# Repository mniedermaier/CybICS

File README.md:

<p align="center">
  <b>A complete industrial facility on your desk. Attack it. Detect it. Defend it.</b><br/>
  Open-source ICS security training, on a Raspberry Pi board or in Docker.<br/>
  <sub>CybICS is pronounced "Cybix".</sub>
</p>

<div align="center">

</div>

---

## What is CybICS?

CybICS (Cybersecurity for Industrial Control Systems) is an open-source training platform designed to help cybersecurity professionals, students, and researchers understand the unique challenges of securing industrial control systems (ICS) and SCADA environments.

The platform recreates a complete industrial facility, from the physical process up to the operator's screen:
- **Physical process** - a gas pressure process with tanks, a compressor and valves, run by an STM32 on the board or simulated in Docker
- **PLC** (Programmable Logic Controller) - OpenPLC
- **HMI** (Human-Machine Interface) - FUXA
- **Gateways and services** - an OPC-UA server and an S7comm endpoint
- **Engineering workstation and attack machine** - the tools of the operator and of the attacker
- **Intrusion detection** - a rule-based IDS watching the plant network
- **Industrial protocols** - Modbus TCP, OPC-UA and S7comm, plus DNP3 and EtherNet/IP via OpenPLC

### Why CybICS?

- **A real plant, not only a VM.** The physical board is the process diagram: LEDs show the tanks, the compressor and the valves as you attack them. The same process runs in Docker when no board is at hand.
- **Learn, attack, detect, defend.** 38 Theory Path lessons, 22 CTF challenges and a built-in IDS, mapped to MITRE ATT&CK for ICS, D3FEND and NIST SP 800-82r3.
- **Real industrial protocols.** Modbus TCP, S7comm and OPC-UA against OpenPLC and a FUXA HMI.
- **Free and open source.** The CybICS hardware, firmware and software are MIT licensed.

---

## Table of Contents

- [What is CybICS?](#what-is-cybics)
- [Deployment Options](#deployment-options)
- [Quick Start - Virtual Testbed](#quick-start---virtual-testbed)
- [Physical Process Description](#physical-process-description)
- [Hardware](#hardware)
- [Software Components](#software-components)
- [Training Modules](#training-modules)
- [Troubleshooting](#troubleshooting)
- [Documentation](#documentation)
- [Abbreviations](#abbreviations)
- [Contributing](#contributing)
- [License](#license)

---

## Deployment Options

CybICS offers two deployment modes to suit different learning needs and budgets:

<table>
<tr>
<td width="50%" valign="top">

### Virtual (Recommended for Beginners)
**Docker-based deployment for easy setup**

</td>
<td width="50%" valign="top">

### Physical (Advanced)
**Hardware-based deployment with Raspberry Pi**

</td>
</tr>
<tr>
<td width="50%" valign="top">

**Advantages**:
- No hardware required
- Quick setup (5 minutes)
- Easy to reset and reproduce
- Suited to classroom and online training
- Runs on Windows, Linux, macOS

</td>
<td width="50%" valign="top">

**Advantages**:
- Realistic physical hardware
- Learn embedded systems security
- Practice hardware attacks (UART, SWD)
- Portable standalone device
- Visual LED indicators

</td>
</tr>
<tr>
<td width="50%" valign="top">

**Requirements**:
- Docker & Docker Compose
- 4GB RAM minimum
- 10GB disk space

</td>
<td width="50%" valign="top">

**Requirements**:
- Raspberry Pi Zero 2 W
- Custom CybICS PCB (~50 EUR)
- LCD display
- MicroSD card

</td>
</tr>
<tr>
<td width="50%" valign="top">

**Use Cases**:
- Learning ICS security fundamentals
- Developing attack/defense techniques
- Classroom training sessions
- CTF competitions

</td>
<td width="50%" valign="top">

**Use Cases**:
- Advanced ICS security training
- Hardware hacking workshops
- Demonstrations at conferences
- Permanent lab installations

</td>
</tr>
</table>

---

## Quick Start - Virtual Testbed

Get CybICS running in under 5 minutes using the virtual environment!

### Prerequisites

- **Docker** and **Docker Compose** installed
- **Git** for cloning the repository
- At least 4GB of free RAM
- Linux, macOS, or Windows with WSL2

### Installation

1. **Clone the repository**:
   ```bash
   git clone https://github.com/mniedermaier/CybICS.git --recursive
   cd CybICS
   ```

2. **Start the virtual environment**:
   ```bash
   ./cybics.sh start
   ```

3. **Access the services**:

   Once started, open your browser and navigate to:

   | Service | URL | Default Credentials |
   |---------|-----|---------------------|
   | **Landing Page** | http://localhost | - |

### Managing the Environment

```bash
# Check status of all services
./cybics.sh status

# View logs from all containers
./cybics.sh logs

# Stop the environment
./cybics.sh stop

# Restart the environment
./cybics.sh restart

# Update Docker images to latest version
./cybics.sh update
```
---

## Physical Process Description

CybICS simulates a gas pressure control system commonly found in industrial environments. This simple yet realistic process provides an excellent foundation for learning ICS cybersecurity concepts.

### System Overview

The system maintains gas pressure in a High Pressure Tank (HPT) using gas from a Gas Storage Tank (GST). A PLC controls a compressor that transfers gas between tanks while monitoring pressure levels and safety conditions.

### Components

#### Gas Storage Tank (GST)
Buffer tank for the external gas supply. The PLC maintains GST pressure between 60-240 bar.

| Pressure | Status | Range (bar) | Color Indicator |
|----------|--------|-------------|-----------------|
| <50 | Low | 0-49 | Red |
| 50-149 | Normal | 50-149 | Green |
| 150+ | Full | 150-255 | Blue |

**Control Loop**:
- When GST < 60 bar → Start filling from external supply
- Continue until GST ≥ 240 bar → Stop filling
- Prevents compressor operation when GST is too low

#### High Pressure Tank (HPT)
Main buffer tank providing pressure to the system. Target range: 60-90 bar.

| Pressure | Status | Range (bar) | Meaning |
|----------|--------|-------------|---------|
| 0 | Empty | 0 | System offline |
| 1-49 | Low | 1-49 | Below operating range |
| 50-99 | Normal | 50-99 | Safe operating range |
| 100-149 | High | 100-149 | Above target, but safe |
| 150+ | Critical | 150+ | Dangerous overpressure |

**Control Loop**:
- When HPT < 60 bar AND GST > 50 bar → Start compressor
- Continue until HPT ≥ 90 bar → Stop compressor
- Compressor disabled if GST < 50 bar (safety interlock)

#### System Operation
The system can operate normally when HPT is between 50-100 bar:
- HPT < 50 bar → System cannot operate (insufficient pressure)
- HPT > 100 bar → System at risk of damage

#### Safety: Blowout Valve (BO)
Mechanical safety valve (not PLC-controlled) that prevents catastrophic failure:
- Opens when HPT > 220 bar
- Vents toxic gas to atmosphere
- Closes when HPT < 200 bar
- **Security implication**: Triggering the blowout releases toxic gas

---

## Hardware

For those choosing the physical deployment, CybICS uses affordable, off-the-shelf components.

**Detailed instructions**: [Hardware Guide](hardware/README.md) | [PCB Ordering Guide](hardware/pcb/README.md)

---

## Training Modules

CybICS includes 13+ hands-on training modules covering the full ICS security lifecycle:

Each module includes:
- Background theory
- Hands-on exercises
- CTF-style flags
- Hints and solutions

**Start training**: [Training Overview](training/README.md)

---

## Documentation

Comprehensive documentation is available for all components:

### Getting Started
- [Quick Start Guide](doc/README.md) - Detailed installation instructions
- [Training Overview](training/README.md) - All training modules
- [Testing Guide](tests/README.md) - Automated testing

### Hardware
- [Hardware Overview](hardware/README.md) - BOM, assembly, specifications
- [PCB Ordering Guide](hardware/pcb/README.md) - Step-by-step JLCPCB ordering
- [3D Case Files](hardware/case/README.md) - Printable enclosure

### Software
- [Software Overview](software/README.md) - Setup and configuration
- [OpenPLC Integration](software/OpenPLC/README.md) - PLC programming and configuration
- [FUXA HMI](software/FUXA/README.md) - HMI configuration
- [Virtual Hardware I/O](software/hwio-virtual/README.md) - Virtual process simulation
- [Raspberry Pi I/O](software/hwio-raspberry/README.md) - Physical hardware interface
- [STM32 Firmware](software/stm32/README.md) - Embedded firmware (Zephyr RTOS)

---

## Abbreviations

| Abbreviation | Full Name | Description |
| ------------ | --------- | ----------- |
| **BO** | Blowout | Safety valve that vents gas at critical pressure |
| **CTF** | Capture The Flag | Security training challenge format |
| **DNP3** | Distributed Network Protocol 3 | SCADA communication protocol |
| **GST** | Gas Storage Tank | Buffer tank for external gas supply |
| **HMI** | Human-Machine Interface | Operator control and monitoring interface |
| **HPT** | High Pressure Tank | Main system pressure buffer |
| **I2C** | Inter-Integrated Circuit | Serial communication protocol |
| **ICS** | Industrial Control System | Systems controlling industrial processes |
| **LED** | Light-Emitting Diode | Visual indicator on hardware |
| **OPC-UA** | OPC Unified Architecture | Industry 4.0 communication standard |
| **PCB** | Printed Circuit Board | CybICS custom hardware board |
| **PLC** | Programmable Logic Controller | Industrial controller (OpenPLC) |
| **RTOS** | Real-Time Operating System | Zephyr (on STM32) |
| **SCADA** | Supervisory Control and Data Acquisition | Industrial monitoring system |
| **STM32** | STMicroelectronics 32-bit MCU | Microcontroller on CybICS PCB |
| **SWD** | Serial Wire Debug | Programming/debugging interface for STM32 |
| **UART** | Universal Asynchronous Receiver-Transmitter | Serial communication |

---

## Contributing

We welcome contributions from the community! Here's how you can help:

### Ways to Contribute

- **Report bugs** via GitHub Issues
- **Suggest features** or improvements
- **Improve documentation** (typos, clarity, examples)
- **Create training modules** for new attack/defense techniques
- **Submit code improvements** via Pull Requests
- **Translate documentation** to other languages

### Development Setup

1. Fork the repository
2. Clone your fork: `git clone --recursive https://github.com/YOUR_USERNAME/CybICS.git`
3. Create a branch: `git checkout -b feature/your-feature-name`
4. Make your changes
5. Start the stack and run the full test suite: `./cybics.sh start && pytest tests/`
6. Commit using [Conventional Commits](https://www.conventionalcommits.org/): `git commit -m "feat(landing): describe the change"`
7. Push: `git push origin feature/your-feature-name`
8. Open a Pull Request describing the cause, the fix and what you verified

Everything in git and on GitHub is written in English. The full set of
conventions, including the places that must be changed together, is in
[CLAUDE.md](CLAUDE.md). It is written for AI assistants but applies to everyone.

---

## Build Status

## License

CybICS is released under the **MIT License**. See [LICENSE](/LICENSE) for details.

### Third-Party Components

- **OpenPLC**: GPL-3.0 License
- **FUXA**: MIT License
- **Zephyr RTOS**: Apache-2.0 License

---

## Acknowledgments

CybICS is developed for educational purposes to improve ICS cybersecurity awareness. Special thanks to the open-source community and all contributors.

**Disclaimer**: This platform is designed for authorized training and education only. Unauthorized use against production systems is illegal and unethical.

---

<p align="center">
  <strong>Ready to start?</strong><br>
  <code>./cybics.sh start</code>
</p>

<p align="center">
  <a href="doc/README.md">Detailed Setup Guide</a> •
  <a href="training/README.md">Training Modules</a> •
  <a href="https://github.com/mniedermaier/CybICS/issues">Report Issues</a>
</p>

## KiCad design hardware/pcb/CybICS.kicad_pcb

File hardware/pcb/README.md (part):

# CybICS PCB Ordering Guide

## Overview
This guide provides detailed instructions for ordering the CybICS PCB from JLCPCB with full assembly service. The PCB is designed to be manufactured and assembled by JLCPCB, eliminating the need for manual soldering.

## PCB Design Files
The PCB is designed using KiCad 10.x and all source files are available in this
directory. The sources are stored in the KiCad 10 file format, so KiCad 8 and 9
cannot open them -- install KiCad 10 or later before doing anything below:
- **Schematic**: Shows the circuit design and connections
- **PCB Layout**: Physical board design with component placement
- **Gerber Files**: Manufacturing files for PCB fabrication
- **BOM (Bill of Materials)**: List of all components
- **CPL (Component Placement List)**: Positions for automated assembly

### Project 3D models

`cybics.3dshapes/` holds the models KiCad does not ship. Each one that was
generated rather than downloaded keeps its build script next to it, so it can
be regenerated instead of being an unmaintainable binary:

| Model | Source | Notes |
|-------|--------|-------|
| `Raspberry_Pi_Zero.step` | `Raspberry_Pi_Zero.build.py` (CadQuery) | J1's second model, so the Pi appears plugged onto the board |
| `LCD1602.step` | `LCD1602.build.py` (CadQuery) | DS1; replaces KiCad's `WC1602A.step` |
| `SW-SMD_8P-...step/.wrl` | vendor download (LCSC C2858287) | navigation switch SW3 |
| `USB_C_Receptacle_G-Switch_GT-USB-7010ASV.wrl` | `easyeda2kicad --lcsc_id=C2988369` | J4; KiCad ships no model for this footprint |

The Pi Zero model sits 11.0 mm above the board: 2.5 mm for the male header body
on the carrier plus 8.5 mm for the socket on the Pi's underside, which is the
standard Pi HAT spacing. The Pi is mounted **component side up** -- despite
"FaceDown" in the footprint name -- so the model puts every part on the top
face. Check `doc/pics/cybics.png` if in doubt; that photograph is what the
model was built against.

Outline, mounting holes and the three edge-connector centres come from the
official mechanical drawing; component positions are measured off that
photograph and agree with the drawing's connector centres to about 0.4 mm,
which is what fixes the scale. The parts are simplified shapes rather than
vendor geometry, but carry the detail that makes a render readable:
silkscreen frame and lettering, plated rings around the mounting holes,
the raspberry on the SiP, a stamped microSD lid, recessed connector
mouths, gold test pads, and passives split into black chip resistors and
pale MLCCs the way the photograph shows them.

The female 2x20 socket on the Pi's underside is modelled, with a hole at each
pin position so it mates with the board's male header instead of intersecting
it. It is drawn 0.05 mm short on purpose: the stock header model's body
measures 2.53 mm rather than the nominal 2.50, which would otherwise leave a
sliver of overlap across the whole connector and make every clash check report
it.

Two caveats. The PCB thickness of 1.4 mm is an assumption, as the drawing does
not state one. And the microSD card protrudes 2.1 mm past the board edge, which
is outside J1's `F.Fab` envelope -- that is real, not an error, and worth
knowing when designing an enclosure.

### The display

KiCad's `Display.3dshapes/WC1602A.step` is one fused solid, so the whole module
takes a single colour: pale green board, grey frame, blank white screen. The
replacement splits it into parts and colours them from the photograph -- dark
green board, black bezel, vivid blue screen -- and draws the characters as a
real 5 x 8 dot matrix, because a smooth outline font does not read as an LCD.
The screen shows `CybICS` and nothing more: the firmware also prints a version
and an uptime there, but both would go stale in a file nobody thinks to
regenerate.

Its envelope was recovered by slicing the stock model in Z and matches it
exactly (80 x 36 x 15 mm), so it drops in at the same place.

Regenerate either model with:

```bash
cd hardware/pcb/cybics.3dshapes
python3 -m venv .venv && .venv/bin/pip install cadquery
.venv/bin/python Raspberry_Pi_Zero.build.py
.venv/bin/python LCD1602.build.py
```

`J4` used to render as nothing at all. The board pointed at
`${KICAD10_3DMODEL_DIR}/Connector_USB.3dshapes/USB_C_Receptacle_G-Switch_GT-USB-7010ASV.step`,
which is exactly what the KiCad 10 library footprint declares -- but that file
does not exist. Not locally, and not upstream: `Connector_USB.3dshapes` holds 13
models in total and none of them is a G-Switch part, so 62 of the library's 75
USB footprints have no model. An earlier note here blamed the Ubuntu package;
that was wrong, `kicad-packages3d` 10.0.6 is complete at 3.2 GB and 7251 STEP
files. Installing more would never have fixed it.

The model now comes from the vendor via `easyeda2kicad`, the same route the
navigation switch took, and lives in `cybics.3dshapes/`.

**Vendor models do not share KiCad's footprint origin.** The EasyEDA footprint
for this part sits 1.325 mm in +Y from the KiCad library one, so the model
carries `(offset (xyz 0 1.325 0))` -- note that the offset's Y is negated
relative to the footprint's Y. The way to check an offset is not to reason about
the sign but to compare extents: with this offset the model spans
x -4.470..4.470 and y -3.675..4.225, against the footprint's `F.Fab` at
x -4.470..4.470 and y -3.675..3.675. X matches exactly and so does the front
edge; the 0.55 mm at the back is the shield tab, which `F.Fab` does not draw.

**A model's `.step` and `.wrl` need not share an origin either.** `SW3`'s do
not: the STEP has its origin at the top of the switch body, the VRML at the
board surface. A Z offset measured on one and applied to the other put the
switch 1.85 mm in the air in every render. The board references the `.wrl`, so
measure that one.

## Prerequisites

### Software Requirements
1. **KiCad** (version 10.0 or later)
   - Download from: https://www.kicad.org/download/
   - Used to view and modify PCB design files
   - On Ubuntu, the KiCad project's PPA carries current releases:
     `sudo add-apt-repository ppa:kicad/kicad-10.0-releases && sudo apt install kicad`

2. **Fabrication Toolkit Plugin** (for KiCad)
   - Install via KiCad Plugin and Content Manager
   - Generates files compatible with JLCPCB

### JLCPCB Account
- Create a free account at: https://jlcpcb.com/
- No credit card required for registration

## Step-by-Step Ordering Process

### Step 1: Open the PCB in KiCad

1. Launch KiCad
2. Open the CybICS project file (`.kicad_pro`)
3. Open the PCB Editor
4. Review the design to ensure it's correct

### Step 2: Install Fabrication Toolkit

1. In KiCad, go to **Tools** → **Plugin and Content Manager**
2. Search for "Fabrication Toolkit"
3. Click "Install" and wait for installation to complete
4. Restart KiCad if prompted

<table align="center"><tr><td align="center" width="9999">
</img>
</td></tr></table>

<table align="center"><tr><td align="center" width="9999">
</img>
</td></tr></table>

### Step 3: Generate Fabrication Files

1. Open the PCB Editor in KiCad
2. Click on the **Fabrication Toolkit** icon in the toolbar
3. Tick **Exclude DNP components from BOM**. This one is **off** by default and
   must be changed. `R40` and `R46` are marked DNP because their absence is what
   encodes hardware v1.1, and the plugin keeps DNP parts out of the CPL
   unconditionally but out of the BOM only when this box is ticked. Leave it off
   and the two files disagree: JLCPCB's BOM/CPL matching then reports
   designators that have no position, which is the failure of #238 with the
   files the other way round.
4. Leave the rest of the export options at their defaults. The plugin targets
   JLCPCB already, so there is no manufacturer to choose -- earlier revisions of
   this guide described a **Manufacturer** dropdown that the plugin does not
   have. In particular leave **Plot all active layers** switched off: this is a
   two-layer board, and enabling it only adds the fabrication and courtyard
   layers to the archive, which JLCPCB does not need.
5. Click **Generate** to create all necessary files

<table align="center"><tr><td align="center" width="9999">
</img>
</td></tr></table>

<table align="center"><tr><td align="center" width="9999">
</img>
</td></tr></table>

The toolkit writes `hardware/pcb/production/` (gitignored):
- `CybICS.zip` - gerbers and the PTH/NPTH drill files
- `bom.csv` - bill of materials, JLCPCB column layout
- `positions.csv` - the CPL
- `designators.csv`, `netlist.ipc` - not needed by JLCPCB

### Generating the same files without the GUI

The plugin ships a CLI, so the set can be regenerated reproducibly -- useful for
checking a change without clicking through the dialog. It needs `pcbnew`, so run
it in the image CI already uses:

```bash
curl -sL https://github.com/bennymeg/Fabrication-Toolkit/archive/refs/tags/5.3.1.tar.gz \
  | tar -xz --one-top-level=ft --strip-components=1
docker run --rm --user $(id -u):$(id -g) -e HOME=/tmp \
  -v "$PWD/ft:/ft" -v "$PWD:/repo" -w /ft setsoft/kicad_auto:ki10 \
  python3 -m plugins.cli -p /repo/hardware/pcb/CybICS.kicad_pcb -t -f -e -nI -nB
```

`-t` and `-f` are the automatic translations and zone fill, which the dialog has
on by default and the CLI does not. `-e` is the DNP exclusion from step 3. The
plugin reads the board and writes `production/`; it does not modify the
schematic, the board or the project file.

Whatever route you take, check the two files agree before uploading:

```bash
python3 - <<'EOF'
import csv
bom=list(csv.DictReader(open('hardware/pcb/production/bom.csv',encoding='utf-8-sig')))
cpl=list(csv.DictReader(open('hardware/pcb/production/positions.csv',encoding='utf-8-sig')))
b={r.strip() for row in bom for r in row['Designator'].split(',')}
c={r['Designator'] for r in cpl}
print('BOM only:', sorted(b-c) or 'none')
print('CPL only:', sorted(c-b) or 'none')
for x in ('R40','R46','FID1','FID2','FID3'):
    assert x not in b and x not in c, x
print('no DNP or fiducials in either file')
EOF
```

### Step 4: Upload to JLCPCB

1. Go to https://jlcpcb.com/
2. Click **Quote Now** or **Instant Quote**
3. Click **Add Gerber File** and upload `gerber.zip`
4. Wait for the system to process the file (~30 seconds)

### Step 5: Configure PCB Options

After upload, configure the following options:

### Step 6: Enable PCB Assembly

1. Scroll down and toggle **PCB Assembly** to ON

### Step 7: Upload BOM and CPL Files

1. Click **Confirm** on the assembly section
2. Upload the BOM file:
   - Click **Add BOM File**
   - Select `bom.csv` from the production folder
3. Upload the CPL file:
   - Click **Add CPL File**
   - Select `positions.csv` from the production folder
4. Click **Process BOM & CPL**

### Step 7b: Check the version straps are not placed

`R40` and `R46` are marked **DNP** -- they encode the hardware revision by
being absent (see [Hardware Version Coding](../README.md#version-coding)).
Confirm they are missing from the uploaded BOM and CPL. Do not take the
plugin's word for it: whether they leave the BOM depends on the checkbox in
step 3, and if JLCPCB places them the board reports code `00000` instead of
`00001` and identifies itself as a revision that does not exist.

Every other `R41`-`R44` and `R47`-`R50` must be placed.

### Step 8: Component Matching

After processing, JLCPCB will display component matching:

1. **Review matched components**:
   - Green checkmark: Component found in JLCPCB inventory
   - Yellow warning: Alternative suggested
   - Red X: Component not available

2. **For unavailable components**:
   - Click on the component row
   - Search for alternatives in JLCPCB library

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
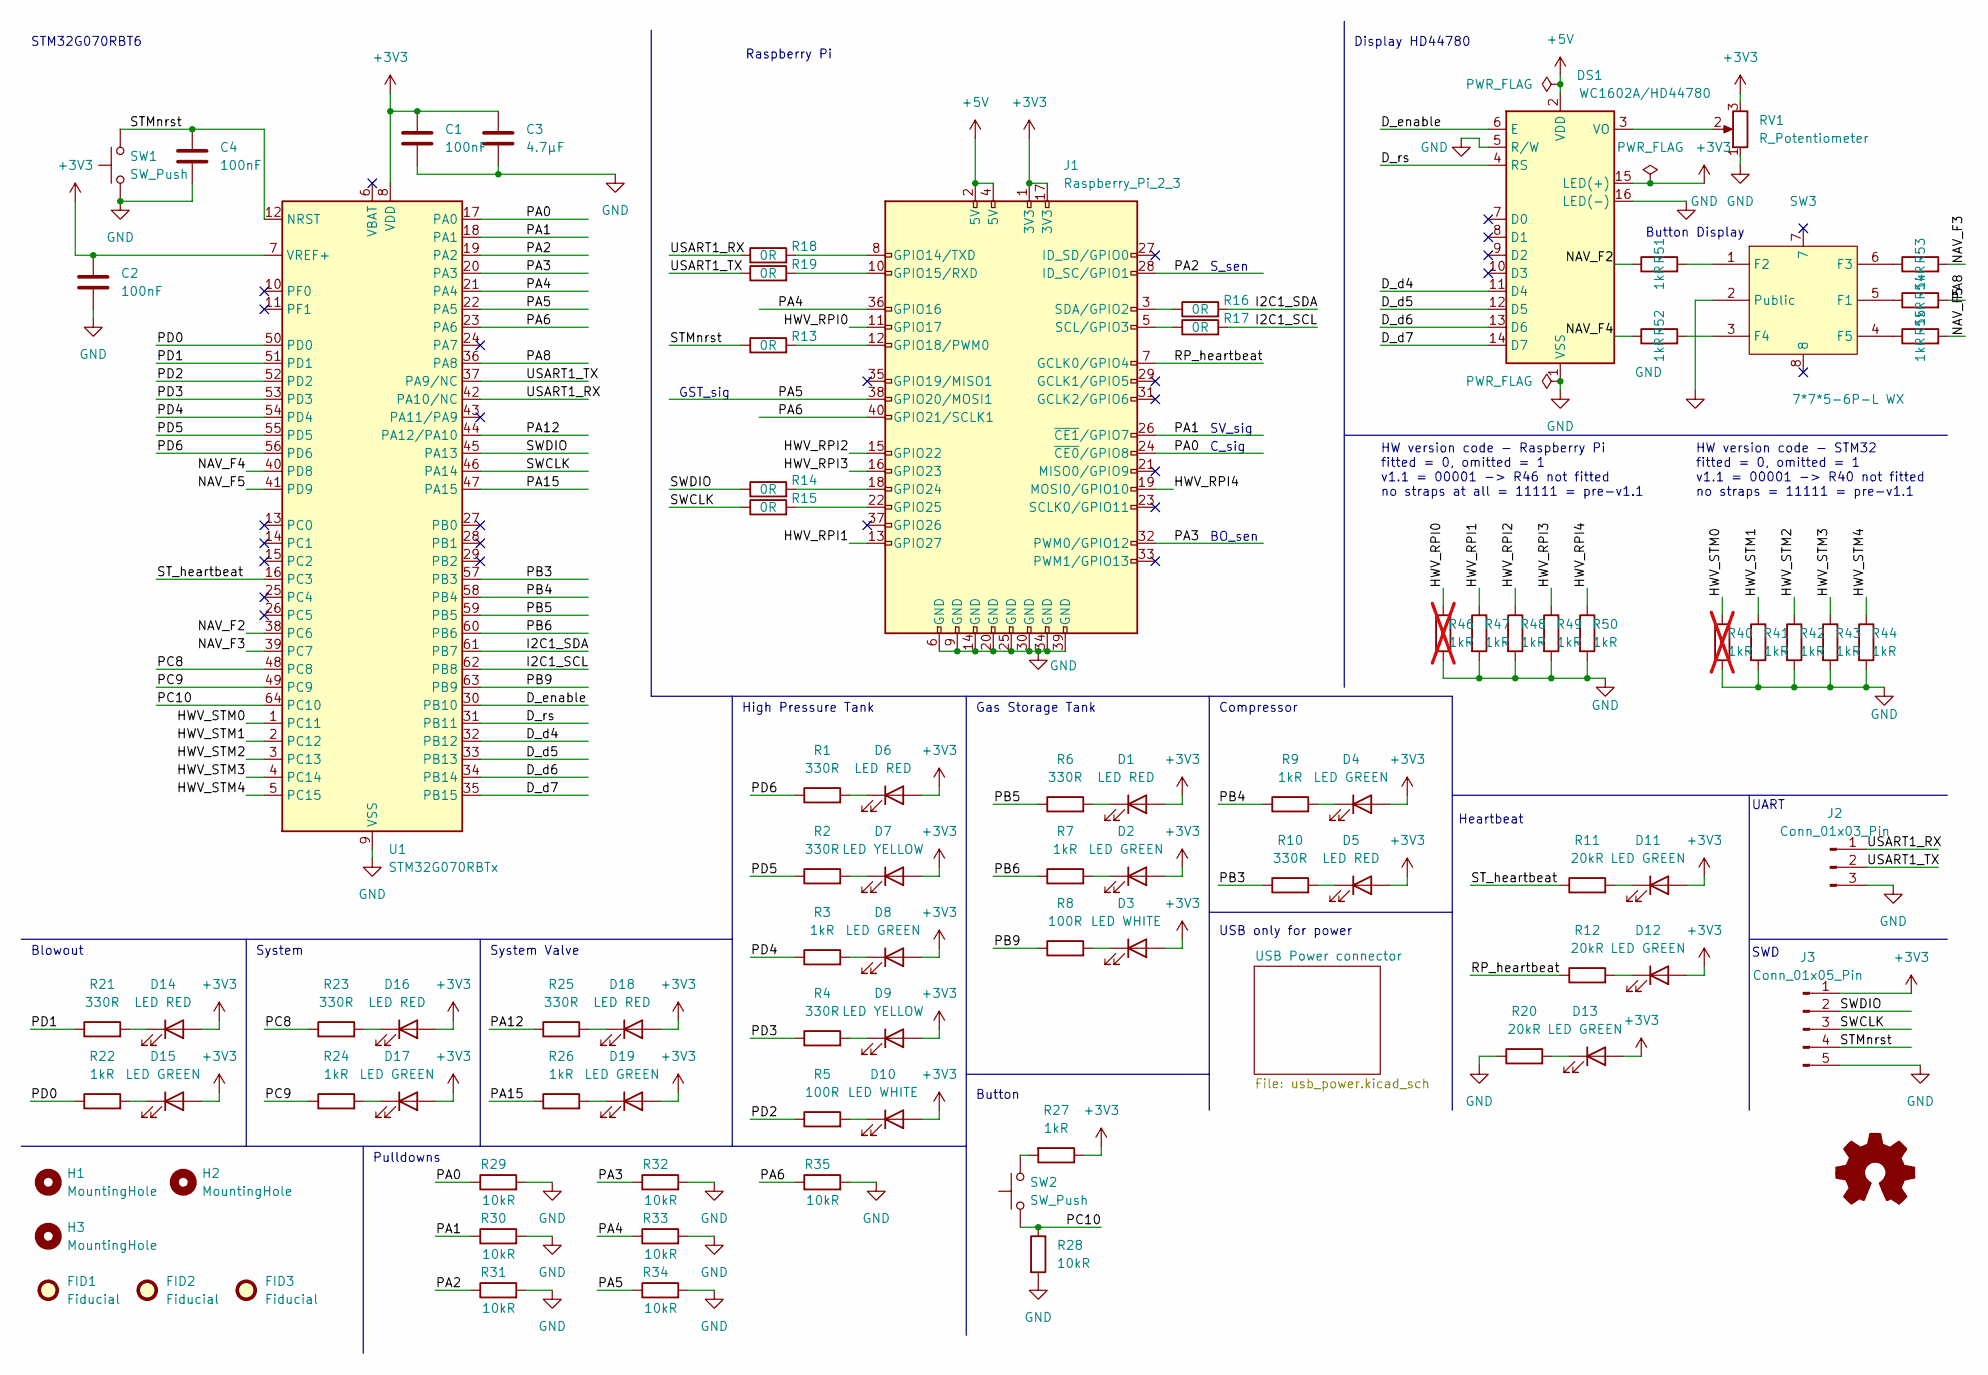
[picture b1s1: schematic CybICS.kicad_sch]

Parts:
C1, C2, C4: 100nF; C_0805_2012Metric_Pad1.18x1.45mm_HandSolder; JLCPCB Part # C49678
C3: 4.7μF; C_0805_2012Metric_Pad1.18x1.45mm_HandSolder; JLCPCB Part # C1779
D1, D5, D6, D14, D16, D18: LED RED; LED_0805_2012Metric_Pad1.15x1.40mm_HandSolder; JLCPCB Part # C84256
D2, D4, D8, D11, D12, D13, D15, D17, D19: LED GREEN; LED_0805_2012Metric_Pad1.15x1.40mm_HandSolder; JLCPCB Part # C2297
D3, D10: LED WHITE; LED_0805_2012Metric_Pad1.15x1.40mm_HandSolder; JLCPCB Part # C34499
D7, D9: LED YELLOW; LED_0805_2012Metric_Pad1.15x1.40mm_HandSolder; JLCPCB Part # C2296
DS1: WC1602A/HD44780; WC1602A; JLCPCB Part # C5307341
FID1, FID2, FID3: Fiducial; Fiducial_1mm_Mask2mm
H1, H2, H3: MountingHole; MountingHole_3.2mm_M3
J1: Raspberry_Pi_2_3; Raspberry_Pi_Zero_Socketed_THT_FaceDown_MountingHoles; JLCPCB Part # C5224014
J2: Conn_01x03_Pin; PinHeader_1x03_P2.54mm_Vertical; JLCPCB Part # C5445396
J3: Conn_01x05_Pin; PinHeader_1x05_P2.54mm_Vertical; JLCPCB Part # C225480
R1, R2, R4, R6, R10, R21, R23, R25: 330R; R_0805_2012Metric_Pad1.20x1.40mm_HandSolder; JLCPCB Part # C17630
R3, R7, R9, R22, R24, R26, R27, R41, R42, R43, R44, R47, R48, R49, R50, R51, R52, R53, R54, R55: 1kR; R_0805_2012Metric_Pad1.20x1.40mm_HandSolder; JLCPCB Part # C17513
R5, R8: 100R; R_0805_2012Metric_Pad1.20x1.40mm_HandSolder; JLCPCB Part # C17408
R11, R12, R20: 20kR; R_0805_2012Metric_Pad1.20x1.40mm_HandSolder; JLCPCB Part # C4328
R13, R14, R15, R16, R17, R18, R19: 0R; R_0805_2012Metric_Pad1.20x1.40mm_HandSolder; JLCPCB Part # C17477
R28, R29, R30, R31, R32, R33, R34, R35: 10kR; R_0805_2012Metric_Pad1.20x1.40mm_HandSolder; JLCPCB Part # C17414
R40, R46: 1kR; R_0805_2012Metric_Pad1.20x1.40mm_HandSolder; JLCPCB Part # C17513; not fitted
RV1: R_Potentiometer; Potentiometer_Bourns_3314J_Vertical; JLCPCB Part # C36376
SW1, SW2: SW_Push; SW_PUSH_6mm_H5mm; JLCPCB Part # C428628
SW3: 7*7*5-6P-L WX; SW-SMD_8P-L7.0-W7.0-P1.40-LS7.4-TL; JLCPCB Part # C2858287
U1: STM32G070RBTx; LQFP-64_10x10mm_P0.5mm; JLCPCB Part # C529340

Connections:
+3V3: C1.1, C2.1, C3.1, D1.2 (A), D2.2 (A), D3.2 (A), D4.2 (A), D5.2 (A), D6.2 (A), D7.2 (A), D8.2 (A), D9.2 (A), D10.2 (A), D11.2 (A), D12.2 (A), D13.2 (A), D14.2 (A), D15.2 (A), D16.2 (A), D17.2 (A), D18.2 (A), D19.2 (A), DS1.15 (LED(+)), J1.1 (3V3), J1.17 (3V3), J3.1, R27.1, RV1.3, U1.7 (VREF+), U1.8 (VDD)
+5V: DS1.2 (VDD), J1.2 (5V), J1.4 (5V); also elsewhere on the board
/D_d4: DS1.11 (D4), U1.32 (PB12)
/D_d5: DS1.12 (D5), U1.33 (PB13)
/D_d6: DS1.13 (D6), U1.34 (PB14)
/D_d7: DS1.14 (D7), U1.35 (PB15)
/D_enable: DS1.6 (E), U1.30 (PB10)
/D_rs: DS1.4 (RS), U1.31 (PB11)
/HWV_RPI0: J1.11 (GPIO17), R46.1
/HWV_RPI1: J1.13 (GPIO27), R47.1
/HWV_RPI2: J1.15 (GPIO22), R48.1
/HWV_RPI3: J1.16 (GPIO23), R49.1
/HWV_RPI4: J1.19 (MOSI0/GPIO10), R50.1
/HWV_STM0: R40.1, U1.1 (PC11)
/HWV_STM1: R41.1, U1.2 (PC12)
/HWV_STM2: R42.1, U1.3 (PC13)
/HWV_STM3: R43.1, U1.4 (PC14)
/HWV_STM4: R44.1, U1.5 (PC15)
/I2C1_SCL: R17.2, U1.62 (PB8)
/I2C1_SDA: R16.2, U1.61 (PB7)
/NAV_F2: R51.1, U1.38 (PC6)
/NAV_F3: R53.2, U1.39 (PC7)
/NAV_F4: R52.1, U1.40 (PD8)
/NAV_F5: R55.2, U1.41 (PD9)
/PA0: J1.24 (~CE0/GPIO8), R29.1, U1.17 (PA0)
/PA1: J1.26 (~CE1/GPIO7), R30.1, U1.18 (PA1)
/PA2: J1.28 (ID_SC/GPIO1), R31.1, U1.19 (PA2)
/PA3: J1.32 (PWM0/GPIO12), R32.1, U1.20 (PA3)
/PA4: J1.36 (GPIO16), R33.1, U1.21 (PA4)
/PA5: J1.38 (GPIO20/MOSI1), R34.1, U1.22 (PA5)
/PA6: J1.40 (GPIO21/SCLK1), R35.1, U1.23 (PA6)
/PA8: R54.2, U1.36 (PA8)
/PA12: R25.1, U1.44 (PA12/PA10)
/PA15: R26.1, U1.47 (PA15)
/PB3: R10.1, U1.57 (PB3)
/PB4: R9.1, U1.58 (PB4)
/PB5: R6.1, U1.59 (PB5)
/PB6: R7.1, U1.60 (PB6)
/PB9: R8.1, U1.63 (PB9)
/PC8: R23.1, U1.48 (PC8)
/PC9: R24.1, U1.49 (PC9)
/PC10: R28.1, SW2.1, U1.64 (PC10)
/PD0: R22.1, U1.50 (PD0)
/PD1: R21.1, U1.51 (PD1)
/PD2: R5.1, U1.52 (PD2)
/PD3: R4.1, U1.53 (PD3)
/PD4: R3.1, U1.54 (PD4)
/PD5: R2.1, U1.55 (PD5)
/PD6: R1.1, U1.56 (PD6)
/RP_heartbeat: J1.7 (GCLK0/GPIO4), R12.1
/STMnrst: C4.1, J3.4, R13.1, SW1.2, U1.12 (NRST)
/ST_heartbeat: R11.1, U1.16 (PC3)
/SWCLK: J3.3, R15.1, U1.46 (PA14)
/SWDIO: J3.2, R14.1, U1.45 (PA13)
/USART1_RX: J2.1, R18.1, U1.42 (PA10/NC)
/USART1_TX: J2.2, R19.1, U1.37 (PA9/NC)
GND: C1.2, C2.2, C3.2, C4.2, DS1.1 (VSS), DS1.5 (R/W), DS1.16 (LED(-)), J1.6 (GND), J1.9 (GND), J1.14 (GND), J1.20 (GND), J1.25 (GND), J1.30 (GND), J1.34 (GND), J1.39 (GND), J2.3, J3.5, R20.1, R28.2, R29.2, R30.2, R31.2, R32.2, R33.2, R34.2, R35.2, R40.2, R41.2, R42.2, R43.2, R44.2, R46.2, R47.2, R48.2, R49.2, R50.2, RV1.1, SW1.1, SW3.2 (Public), U1.9 (VSS); also elsewhere on the board
unnamed: D1.1 (K), R6.2
unnamed: D2.1 (K), R7.2
unnamed: D3.1 (K), R8.2
unnamed: D4.1 (K), R9.2
unnamed: D5.1 (K), R10.2
unnamed: D6.1 (K), R1.2
unnamed: D7.1 (K), R2.2
unnamed: D8.1 (K), R3.2
unnamed: D9.1 (K), R4.2
unnamed: D10.1 (K), R5.2
unnamed: D11.1 (K), R11.2
unnamed: D12.1 (K), R12.2
unnamed: D13.1 (K), R20.2
unnamed: D14.1 (K), R21.2
unnamed: D15.1 (K), R22.2
unnamed: D16.1 (K), R23.2
unnamed: D17.1 (K), R24.2
unnamed: D18.1 (K), R25.2
unnamed: D19.1 (K), R26.2
unnamed: DS1.3 (VO), RV1.2
unnamed: J1.8 (GPIO14/TXD), R18.2
unnamed: J1.10 (GPIO15/RXD), R19.2
unnamed: J1.12 (GPIO18/PWM0), R13.2
unnamed: J1.18 (GPIO24), R14.2
unnamed: J1.22 (GPIO25), R15.2
unnamed: J1.5 (SCL/GPIO3), R17.1
unnamed: J1.3 (SDA/GPIO2), R16.1
unnamed: R27.2, SW2.2
unnamed: R54.1, SW3.5 (F1)
unnamed: R51.2, SW3.1 (F2)
unnamed: R53.1, SW3.6 (F3)
unnamed: R52.2, SW3.3 (F4)
unnamed: R55.1, SW3.4 (F5)

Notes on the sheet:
UART
Gas Storage Tank
HW version code - STM32 fitted = 0, omitted = 1 v1.1 = 00001 -> R40 not fitted no straps = 11111 = pre-v1.1
System
High Pressure Tank
STM32G070RBT6
Heartbeat
System Valve
GST_sig
Button
SWD
Display HD44780
Pulldowns
Raspberry Pi
C_sig
HW version code - Raspberry Pi fitted = 0, omitted = 1 v1.1 = 00001 -> R46 not fitted no straps at all = 11111 = pre-v1.1
SV_sig
S_sen
BO_sen
Button Display
USB only for power
Blowout
Compressor

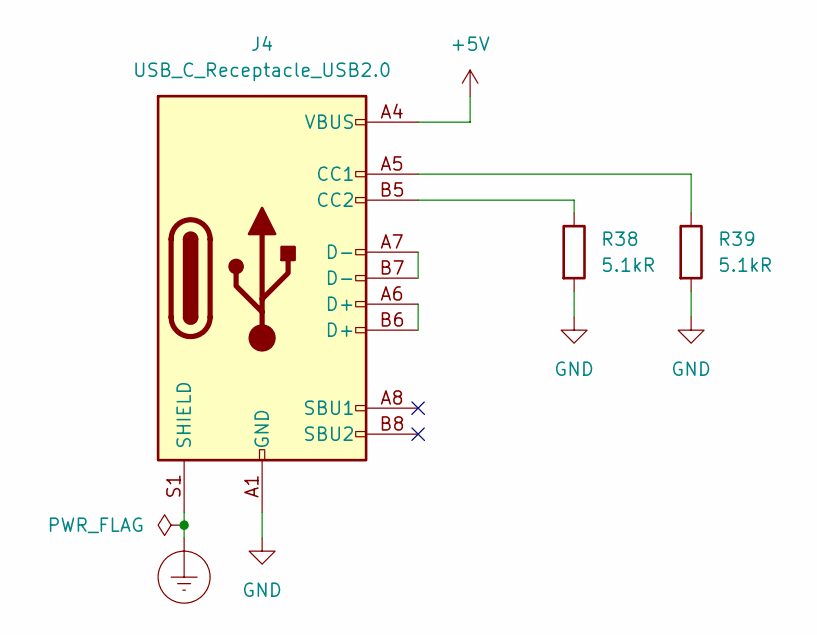
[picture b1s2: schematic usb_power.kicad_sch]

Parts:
J4: USB_C_Receptacle_USB2.0; USB_C_Receptacle_G-Switch_GT-USB-7010ASV; JLCPCB Part # C2988369
R38, R39: 5.1kR; R_0805_2012Metric_Pad1.20x1.40mm_HandSolder; JLCPCB Part # C27834

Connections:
+5V: J4.A4 (VBUS), J4.A9 (VBUS), J4.B4 (VBUS), J4.B9 (VBUS); also elsewhere on the board
Earth_Protective: J4.S1 (SHIELD)
GND: J4.A1 (GND), J4.A12 (GND), J4.B1 (GND), J4.B12 (GND), R38.2, R39.2; also elsewhere on the board
unnamed: J4.A5 (CC1), R39.1
unnamed: J4.B5 (CC2), R38.1
unnamed: J4.A6 (D+), J4.B6 (D+)
unnamed: J4.A7 (D-), J4.B7 (D-)

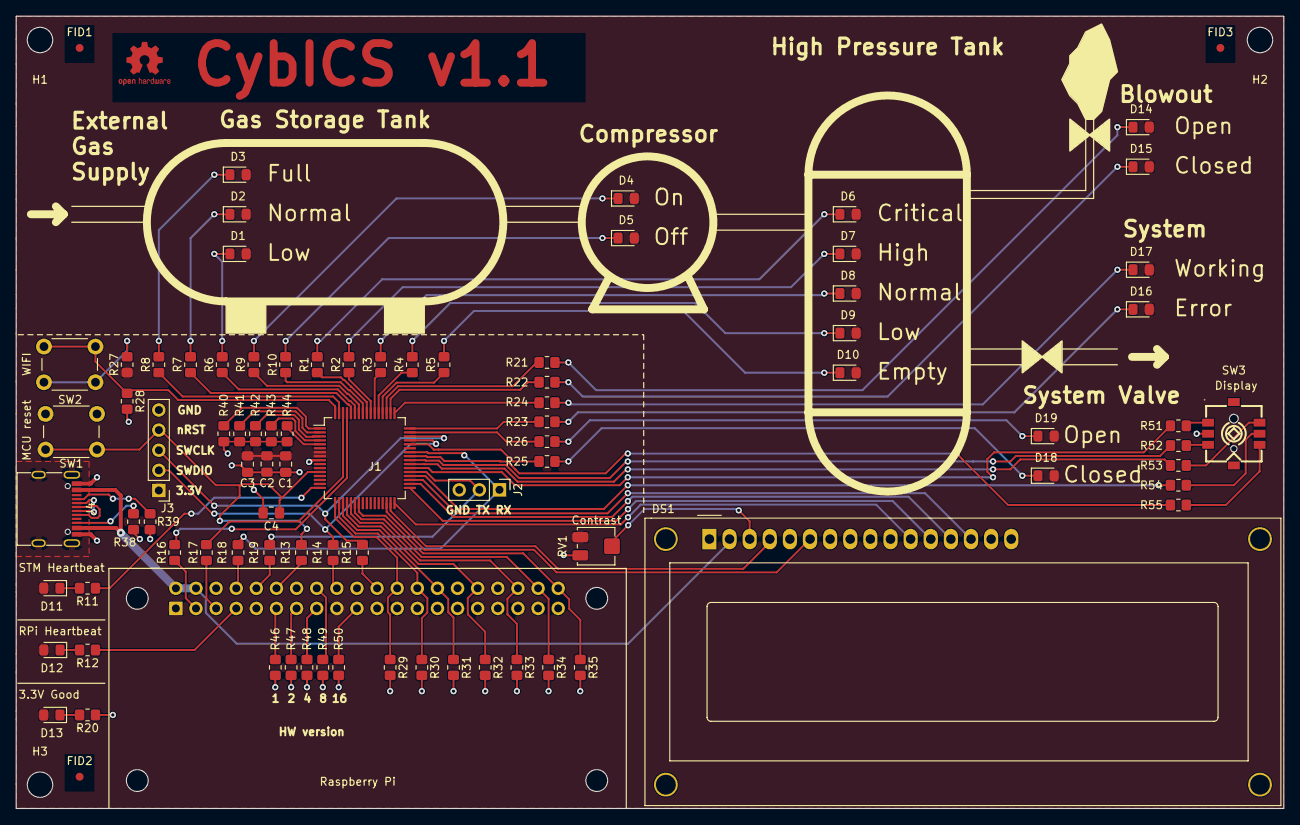
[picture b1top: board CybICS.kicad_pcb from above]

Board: 2 copper layers, 160.0 x 100.0 mm, 91 parts (0 on the bottom side), 94 nets.

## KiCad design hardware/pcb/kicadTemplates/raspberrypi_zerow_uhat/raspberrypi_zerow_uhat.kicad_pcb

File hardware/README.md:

## Hardware  
The hardware was kept simple and cost-efficient.
All you need is the CybICS baseboard, a Raspberry Pi Zero 2 W and a 1602 display.
For the physical process visualization on the PCB a few LEDs are used.

<table align="center"><tr><td align="center" width="9999">
</img>
</td></tr></table>

The PCB can be ordered completly assembled at [JLCPCB](https://jlcpcb.com/).
The total cost for a testbed is around 50 euros.
However, the minimum purchase of PCBs is 5 pieces when ordered from [JLCPCB](https://jlcpcb.com/).

### Components
The hardware consists of three core components.
Additionally, there is a 3D printable case,
which makes desk usage easier ([link](case/README.md)).

| Component        | Description                             |
| ---------------- | --------------------------------------- |
| Base Board       | Simulating the physical process         |
| Raspberry Pi     | Controlling the physical process        |
| Display          | HD44780 1602 LCD showing physical state |

## Bill of Materials (BOM)

### Required Components

| Item | Quantity | Description | Approx. Cost (EUR) | Notes |
|------|----------|-------------|-------------------|-------|
| **CybICS PCB** | 1 | Custom PCB with STM32G070RBT6 | ~40 | Min. order 5 pieces from JLCPCB |
| **Raspberry Pi Zero 2 W** | 1 | 1GHz quad-core ARM Cortex-A53 | ~15 | Includes WiFi and Bluetooth |
| **1602 LCD Display** | 1 | HD44780 compatible, I2C interface | ~3 | Blue or green backlight |
| **MicroSD Card** | 1 | 8GB or larger, Class 10 | ~5 | For Raspberry Pi OS |
| **USB-C Cable** | 1 | Power supply cable | ~3 | 5V/2A minimum |
| **Pin Headers** | 1 set | 2.54mm pitch headers for Raspberry Pi | ~2 | Usually included with RPi |

**Total Estimated Cost**: ~50-70 EUR per complete unit

### Optional Components

| Item | Quantity | Description | Approx. Cost (EUR) | Notes |
|------|----------|-------------|-------------------|-------|
| **3D Printed Case** | 1 | Protective enclosure | ~5 | Filament + printing time |
| **Stand/Base** | 1 | Simple display stand | ~2 | See standSimple/ directory |
| **USB Power Adapter** | 1 | 5V/2.5A wall adapter | ~5 | If not using PC USB |

### Where to Buy

#### PCB Manufacturing
- **JLCPCB**: https://jlcpcb.com/ (Recommended - full assembly available)
  - Upload Gerber files from `hardware/pcb/` directory
  - Select assembly service (PCBA)
  - Minimum order: 5 boards
  - Lead time: ~2 weeks

#### Raspberry Pi
- **Official Raspberry Pi Resellers**: https://www.raspberrypi.com/products/
- Local electronics distributors (varies by country)

#### LCD Display
- Common suppliers: AliExpress, Amazon, local electronics shops
- Search for: "1602 LCD I2C" or "1602A LCD module"

#### MicroSD Card
- Any reputable brand (SanDisk, Samsung, Kingston)
- Minimum 8GB, Class 10 or better recommended

## Hardware Version Coding  

From v1.1 the board carries its revision as a 5-bit code that both controllers
can read back, so firmware can adapt without being told which board it runs on.

Each bit is one 1 k resistor to GND, read against the controller's internal
pull-up: **fitted = 0, omitted = 1**. A new revision therefore only changes
which resistors are placed -- no schematic or layout edit.

| Bit | STM32 | pin | Raspberry Pi | pin |
|-----|-------|-----|--------------|-----|
| 0   | R40   | PC11 | R46 | GPIO17 |
| 1   | R41   | PC12 | R47 | GPIO27 |
| 2   | R42   | PC13 | R48 | GPIO22 |
| 3   | R43   | PC14 | R49 | GPIO23 |
| 4   | R44   | PC15 | R50 | GPIO10 |

Both sides carry the same code, so one resistor per side is omitted for a
given revision.

| Code | Revision |
|------|----------|
| `00001` (1) | v1.1 -- R40 and R46 omitted |
| `11111` (31) | **no straps fitted** -- a pre-v1.1 board, or a new board with the straps missing |

`11111` is what a v1.0 board reads by itself: the resistor footprints do not
exist there, so the pins float and the pull-ups win. Do not assign 31 to a real
revision. Note that a v1.1 board assembled without any straps is
indistinguishable from a v1.0 board.

Firmware must enable the internal pull-up on these pins before reading them.

Both sides read them: `software/stm32/src/hw_version.c` for the STM32's copy and
`software/hwio-raspberry/hw_version.py` for the Pi's. The Pi publishes what it
finds to the landing page, under *Settings -> Board Revision*.

The firmware does not simply read them, though: it probes each pin against both
internal pulls, so it can tell a fitted resistor (holds the pin low either way)
from an empty footprint (follows the pull). That is what lets it count how many
of the five are actually soldered, and a board with **none** fitted is then
resolved through `PA8`, which v1.0 loads with `R36` and v1.1 does not. See
[Front Panel and Board Revision Detection](../software/stm32/README.md#board-revision-detection).

So a v1.1 board assembled without straps is no longer silently mistaken for a
v1.0 board -- it is detected, and the firmware says so in the boot log. Fit
`R41`-`R44` anyway: the probe is a safety net, not a substitute, and it cannot
work while somebody is holding the navigation switch during boot.

## Upgrading and Modifications

### Using Different Raspberry Pi Models
The hardware is designed for Raspberry Pi Zero 2 W but can work with:
- **Raspberry Pi Zero W**: Lower performance but compatible
- **Raspberry Pi 3/4**: Will not perfectly fit

### Custom PCB Modifications
The KiCad project files in `hardware/pcb/` can be modified to:
- Add additional sensors or actuators
- Change LED colors or positions
- Modify STM32 pinout
- Add expansion connectors

## Safety Considerations

⚠️ **Important Safety Notes**:
- Use only 5V power supplies - higher voltages will damage components
- Do not connect/disconnect components while powered
- Ensure proper ESD (electrostatic discharge) precautions when handling PCB
- Keep away from water and conductive materials
- Do not modify PCB traces without proper knowledge

## Support and Resources

- **PCB Design Files**: See `hardware/pcb/` directory
- **3D Case Files**: See `hardware/case/` directory
- **Schematic PDF**: Available in `hardware/pcb/` directory
- **STM32 Firmware**: See `software/stm32/` directory
- **Assembly Guide**: This document

For technical support, please open an issue on the GitHub repository.

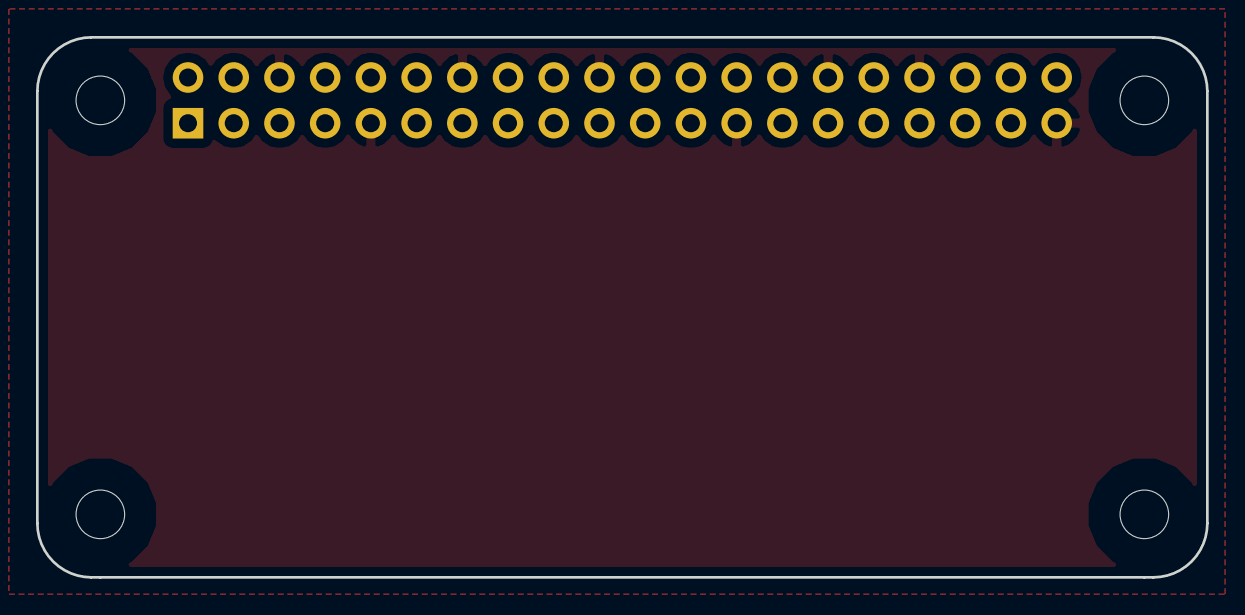
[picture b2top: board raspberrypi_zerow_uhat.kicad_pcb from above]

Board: 2 copper layers, 65.0 x 30.0 mm, 5 parts (1 on the bottom side), 3 nets, no tracks yet.

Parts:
H1, H2, H3, H4: MountingHole; MountingHole_2.7mm_M2.5_uHAT_RPi
J1: GPIO_CONNECTOR; PinSocket_2x20_P2.54mm_Vertical_Centered_Anchor

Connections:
+3V3: J1.1, J1.17
+5V: J1.2, J1.4
GND: J1.6, J1.9, J1.14, J1.20, J1.25, J1.30, J1.34, J1.39

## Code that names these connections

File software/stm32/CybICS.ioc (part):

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Mcu.Name=STM32G070RBTx
Mcu.Package=LQFP64
Mcu.UserName=STM32G070RBTx
PA0.GPIOParameters=GPIO_Label
PA0.GPIO_Label=C_sig
PA0.Signal=GPIO_Input
PA1.GPIOParameters=GPIO_Label
PA1.GPIO_Label=SV_sig
PA1.Signal=GPIO_Input
PA10.GPIOParameters=GPIO_FMPA10,GPIO_Speed,GPIO_PuPd
PA10.GPIO_FMPA10=SYSCFG_FASTMODEPLUS_PA10
PA10.GPIO_PuPd=GPIO_PULLUP
PA10.GPIO_Speed=GPIO_SPEED_FREQ_VERY_HIGH
PA10.Mode=Asynchronous
PA10.Signal=USART1_RX
PA12\ [PA10].GPIOParameters=GPIO_Label
PA12\ [PA10].GPIO_Label=SV_red
PA12\ [PA10].Signal=GPIO_Output
PA13.Mode=Serial_Wire
PA13.Signal=SYS_SWDIO
PA14-BOOT0.Mode=Serial_Wire
PA14-BOOT0.Signal=SYS_SWCLK
PA15.GPIOParameters=GPIO_Label
PA15.GPIO_Label=SV_green
PA15.Signal=GPIO_Output
PA2.GPIOParameters=GPIO_Label
PA2.GPIO_Label=S_sen
PA2.Signal=GPIO_Output
PA3.GPIOParameters=GPIO_Label
PA3.GPIO_Label=BO_sen
PA3.Signal=GPIO_Output
PA4.Signal=GPIO_Input
PA5.GPIOParameters=GPIO_Label
PA5.GPIO_Label=GST_sig
PA5.Signal=GPIO_Input
PA6.Signal=GPIO_Input
PA8.GPIOParameters=GPIO_Label
PA8.GPIO_Label=Display_in
PA8.Signal=GPIO_Input
PA9.GPIOParameters=GPIO_Speed,GPIO_PuPd,GPIO_FMPA9
PA9.GPIO_FMPA9=SYSCFG_FASTMODEPLUS_PA9
PA9.GPIO_PuPd=GPIO_PULLUP
PA9.GPIO_Speed=GPIO_SPEED_FREQ_VERY_HIGH
PA9.Mode=Asynchronous
PA9.Signal=USART1_TX
PB10.GPIOParameters=GPIO_Label
PB10.GPIO_Label=D_enable
PB10.Signal=GPIO_Output
PB11.GPIOParameters=GPIO_Label
PB11.GPIO_Label=D_rs
PB11.Signal=GPIO_Output
PB12.GPIOParameters=GPIO_Label
PB12.GPIO_Label=D_d4
PB12.Signal=GPIO_Output
PB13.GPIOParameters=GPIO_Label
PB13.GPIO_Label=D_d5
PB13.Signal=GPIO_Output
PB14.GPIOParameters=GPIO_Label
PB14.GPIO_Label=D_d6
PB14.Signal=GPIO_Output
PB15.GPIOParameters=GPIO_Label
PB15.GPIO_Label=D_d7
PB15.Signal=GPIO_Output
PB3.GPIOParameters=GPIO_Label
PB3.GPIO_Label=C_off
PB3.Signal=GPIO_Output
PB4.GPIOParameters=GPIO_Label
PB4.GPIO_Label=C_on
PB4.Signal=GPIO_Output
PB5.GPIOParameters=GPIO_Label
PB5.GPIO_Label=GST_low
PB5.Signal=GPIO_Output
PB6.GPIOParameters=GPIO_Label
PB6.GPIO_Label=GST_normal
PB6.Signal=GPIO_Output
PB7.GPIOParameters=GPIO_Speed,GPIO_Pu,GPIO_Mode
PB7.GPIO_Mode=GPIO_MODE_AF_OD
PB7.GPIO_Pu=GPIO_NOPULL
PB7.GPIO_Speed=GPIO_SPEED_FREQ_LOW
PB7.Mode=I2C
PB7.Signal=I2C1_SDA
PB8.GPIOParameters=GPIO_Speed,GPIO_Pu,GPIO_Mode
PB8.GPIO_Mode=GPIO_MODE_AF_OD
PB8.GPIO_Pu=GPIO_NOPULL
PB8.GPIO_Speed=GPIO_SPEED_FREQ_LOW
PB8.Mode=I2C
PB8.Signal=I2C1_SCL
PB9.GPIOParameters=GPIO_Label
PB9.GPIO_Label=GST_full
PB9.Signal=GPIO_Output
PC10.GPIOParameters=GPIO_Label
PC10.GPIO_Label=button
PC10.Signal=GPIO_Input
PC3.GPIOParameters=GPIO_Label
PC3.GPIO_Label=ST_heartbeat
PC3.Signal=GPIO_Output
PC8.GPIOParameters=GPIO_Label
PC8.GPIO_Label=S_red
PC8.Signal=GPIO_Output
PC9.GPIOParameters=GPIO_Label
PC9.GPIO_Label=S_green
PC9.Signal=GPIO_Output
PD0.GPIOParameters=GPIO_Label
PD0.GPIO_Label=BO_green
PD0.Signal=GPIO_Output
PD1.GPIOParameters=GPIO_Label
PD1.GPIO_Label=BO_red
PD1.Signal=GPIO_Output
PD2.GPIOParameters=GPIO_Label
PD2.GPIO_Label=HPT_empty
PD2.Signal=GPIO_Output
PD3.GPIOParameters=GPIO_Label
PD3.GPIO_Label=HPT_low
PD3.Signal=GPIO_Output
PD4.GPIOParameters=GPIO_Label
PD4.GPIO_Label=HPT_normal
PD4.Signal=GPIO_Output
PD5.GPIOParameters=GPIO_Label
PD5.GPIO_Label=HPT_high
PD5.Signal=GPIO_Output
PD6.GPIOParameters=GPIO_Label
PD6.GPIO_Label=HPT_critical
PD6.Signal=GPIO_Output
RCC.HSE_VALUE=8000000
RCC.SYSCLKFreq_VALUE=64000000
RCC.SYSCLKSource=RCC_SYSCLKSOURCE_PLLCLK
board=custom

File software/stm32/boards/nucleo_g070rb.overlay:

/*
 * Copyright (c) 2024 CybICS
 * SPDX-License-Identifier: Apache-2.0
 */

/ {
	aliases {
		led-heartbeat = &heartbeat_led;
	};

	cybics_gpios {
		compatible = "cybics-gpio-group";

		/* Heartbeat LED */
		heartbeat_led: heartbeat_led {
			gpios = <&gpioc 3 GPIO_ACTIVE_HIGH>;
			label = "Heartbeat LED";
		};

		/* Compressor signals */
		c_sig: c_sig {
			gpios = <&gpioa 0 GPIO_ACTIVE_HIGH>;
			label = "Compressor Signal Input";
		};

		c_on: c_on {
			gpios = <&gpiob 4 GPIO_ACTIVE_HIGH>;
			label = "Compressor On LED";
		};

		c_off: c_off {
			gpios = <&gpiob 3 GPIO_ACTIVE_HIGH>;
			label = "Compressor Off LED";
		};

		/* System Valve */
		sv_sig: sv_sig {
			gpios = <&gpioa 1 GPIO_ACTIVE_HIGH>;
			label = "System Valve Signal Input";
		};

		sv_red: sv_red {
			gpios = <&gpioa 12 GPIO_ACTIVE_HIGH>;
			label = "System Valve Red LED";
		};

		sv_green: sv_green {
			gpios = <&gpioa 15 GPIO_ACTIVE_HIGH>;
			label = "System Valve Green LED";
		};

		/* System */
		s_sen: s_sen {
			gpios = <&gpioa 2 GPIO_ACTIVE_HIGH>;
			label = "System Sensor Output";
		};

		s_red: s_red {
			gpios = <&gpioc 8 GPIO_ACTIVE_HIGH>;
			label = "System Red LED";
		};

		s_green: s_green {
			gpios = <&gpioc 9 GPIO_ACTIVE_HIGH>;
			label = "System Green LED";
		};

		/* Blow Out */
		bo_sen: bo_sen {
			gpios = <&gpioa 3 GPIO_ACTIVE_HIGH>;
			label = "Blow Out Sensor Output";
		};

		bo_red: bo_red {
			gpios = <&gpiod 1 GPIO_ACTIVE_HIGH>;
			label = "Blow Out Red LED";
		};

		bo_green: bo_green {
			gpios = <&gpiod 0 GPIO_ACTIVE_HIGH>;
			label = "Blow Out Green LED";
		};

		/* Gas Storage Tank */
		gst_sig: gst_sig {
			gpios = <&gpioa 5 GPIO_ACTIVE_HIGH>;
			label = "GST Signal Input";
		};

		gst_low: gst_low {
			gpios = <&gpiob 5 GPIO_ACTIVE_HIGH>;
			label = "GST Low LED";
		};

		gst_normal: gst_normal {
			gpios = <&gpiob 6 GPIO_ACTIVE_HIGH>;
			label = "GST Normal LED";
		};

		gst_full: gst_full {
			gpios = <&gpiob 9 GPIO_ACTIVE_HIGH>;
			label = "GST Full LED";
		};

		/* High Pressure Tank */
		hpt_empty: hpt_empty {
			gpios = <&gpiod 2 GPIO_ACTIVE_HIGH>;
			label = "HPT Empty LED";
		};

		hpt_low: hpt_low {
			gpios = <&gpiod 3 GPIO_ACTIVE_HIGH>;
			label = "HPT Low LED";
		};

		hpt_normal: hpt_normal {
			gpios = <&gpiod 4 GPIO_ACTIVE_HIGH>;
			label = "HPT Normal LED";
		};

		hpt_high: hpt_high {
			gpios = <&gpiod 5 GPIO_ACTIVE_HIGH>;
			label = "HPT High LED";
		};

		hpt_critical: hpt_critical {
			gpios = <&gpiod 6 GPIO_ACTIVE_HIGH>;
			label = "HPT Critical LED";
		};

		/* Display */
		d_enable: d_enable {
			gpios = <&gpiob 10 GPIO_ACTIVE_HIGH>;
			label = "Display Enable";
		};

		d_rs: d_rs {
			gpios = <&gpiob 11 GPIO_ACTIVE_HIGH>;
			label = "Display RS";
		};

		d_d4: d_d4 {
			gpios = <&gpiob 12 GPIO_ACTIVE_HIGH>;
			label = "Display D4";
		};

		d_d5: d_d5 {
			gpios = <&gpiob 13 GPIO_ACTIVE_HIGH>;
			label = "Display D5";
		};

		d_d6: d_d6 {
			gpios = <&gpiob 14 GPIO_ACTIVE_HIGH>;
			label = "Display D6";
		};

		d_d7: d_d7 {
			gpios = <&gpiob 15 GPIO_ACTIVE_HIGH>;
			label = "Display D7";
		};

	};

	/*
	 * The board's actual buttons.
	 *
	 * Kept apart from cybics_gpios so that "gpio-keys" covers only things
	 * that really are keys.  Nothing binds this today -- the application
	 * polls the pins itself in ui_input.c, because the pull-up and the
	 * polarity differ between board revisions and the devicetree cannot
	 * express a runtime choice.  See ui_input.c for why.
	 *
	 * display_in is the front-panel switch on both revisions:
	 *   v1.0  a discrete push-button, 3V3 -> R37 -> SW3 -> PA8 with R36
	 *         to GND.  Pressed reads high, and an internal pull-up would
	 *         fight R36.
	 *   v1.1+ contact F1, the centre press of the 5-way navigation switch,
	 *         whose common is tied to GND.  Pressed reads low and the pin
	 *         needs the internal pull-up.
	 *
	 * nav_up..nav_right exist only from v1.1.  On a v1.0 board PC6, PC7,
	 * PD8 and PD9 are unconnected, so ui_input.c leaves them unconfigured
	 * there rather than reading four floating pins.
	 */
	cybics_keys {
		compatible = "gpio-keys";

		display_in: display_in {
			gpios = <&gpioa 8 GPIO_ACTIVE_HIGH>;
			label = "Display switch (v1.0 button / v1.1 centre)";
		};

		button: button {
			gpios = <&gpioc 10 GPIO_ACTIVE_HIGH>;
			label = "WiFi Mode Button";
		};

		/*
		 * Navigation switch directions, v1.1 and newer.
		 *
		 * Contact-to-direction comes from the SHOU HAN 7x7x5-6P-L WX
		 * outline drawing (LCSC C2858287, sheet KFC-A07-02-02-2CL): the
		 * moving contact is a diamond and F2, F3, F5, F4 sit clockwise
		 * from its upper-left face, with pins 1..3 on the west edge and
		 * 4..6 on the east.  SW3 is placed unrotated with its locating
		 * posts north and south, so that order maps to up, right, down,
		 * left as seen by someone facing the board.
		 *
		 * ACTIVE_LOW because the switch common is GND.  The pull-up is
		 * applied at runtime, not here, so that one image still serves
		 * v1.0 -- see ui_input.c.
		 */
		nav_up: nav_up {
			gpios = <&gpioc 6 GPIO_ACTIVE_LOW>;
			label = "Navigation up (SW3 F2)";
		};

		nav_right: nav_right {
			gpios = <&gpioc 7 GPIO_ACTIVE_LOW>;
			label = "Navigation right (SW3 F3)";
		};

		nav_down: nav_down {
			gpios = <&gpiod 9 GPIO_ACTIVE_LOW>;
			label = "Navigation down (SW3 F5)";
		};

		nav_left: nav_left {
			gpios = <&gpiod 8 GPIO_ACTIVE_LOW>;
			label = "Navigation left (SW3 F4)";
		};
	};

	/*
	 * Hardware version straps, PC11..PC15 = bit 0..4.
	 *
	 * Each bit is one 1k resistor to GND.  ACTIVE_HIGH makes
	 * gpio_pin_get_dt() return the bit value directly: a fitted strap
	 * holds the pin low (bit 0), an absent one lets the internal pull-up
	 * win (bit 1).
	 *
	 * No GPIO_PULL_UP here, deliberately.  hw_version.c probes each strap
	 * with the pull-down and then the pull-up to tell a fitted resistor
	 * from an unconnected pin, and a pull specified in the devicetree
	 * would be ORed into both configurations and break the pull-down half
	 * of that probe.
	 *
	 * A pre-v1.1 board has no strap footprints at all, so all five pins
	 * float high and read 0b11111.  See the table in
	 * hardware/README.md#version-coding.
	 *
	 * PC14/PC15 double as the LSE oscillator pins; that is safe here
	 * because the board has no crystal and clk_lse stays disabled.
	 */
	cybics_straps {
		compatible = "cybics-gpio-group";

		hw_ver0: hw_ver0 {
			gpios = <&gpioc 11 GPIO_ACTIVE_HIGH>;
			label = "HW version strap bit 0";
		};

		hw_ver1: hw_ver1 {
			gpios = <&gpioc 12 GPIO_ACTIVE_HIGH>;
			label = "HW version strap bit 1";
		};

		hw_ver2: hw_ver2 {
			gpios = <&gpioc 13 GPIO_ACTIVE_HIGH>;
			label = "HW version strap bit 2";
		};

		hw_ver3: hw_ver3 {
			gpios = <&gpioc 14 GPIO_ACTIVE_HIGH>;
			label = "HW version strap bit 3";
		};

		hw_ver4: hw_ver4 {
			gpios = <&gpioc 15 GPIO_ACTIVE_HIGH>;
			label = "HW version strap bit 4";
		};
	};
};

&usart1 {
	status = "okay";
	current-speed = <115200>;
	/* Use PA9/PA10 like the original FreeRTOS version, not PC4/PC5 */
	pinctrl-0 = <&usart1_tx_pa9 &usart1_rx_pa10>;
	pinctrl-names = "default";
};

&i2c1 {
	status = "okay";
	clock-frequency = <I2C_BITRATE_STANDARD>;
	/* Use PB8/PB7 for I2C1 (SCL/SDA) - matching FreeRTOS pinout */
	pinctrl-0 = <&i2c1_scl_pb8 &i2c1_sda_pb7>;
	pinctrl-names = "default";
};

/* Redirect console to USART1 so debug output is visible */
/ {
	chosen {
		zephyr,console = &usart1;
		zephyr,shell-uart = &usart1;
	};
};

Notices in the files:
README.md:
License: MIT License
hardware/pcb/kicadTemplates/raspberrypi_zerow_uhat/raspberrypi_zerow_uhat.kicad_pcb:
This PCB design is licensed under MIT Open Source License.
